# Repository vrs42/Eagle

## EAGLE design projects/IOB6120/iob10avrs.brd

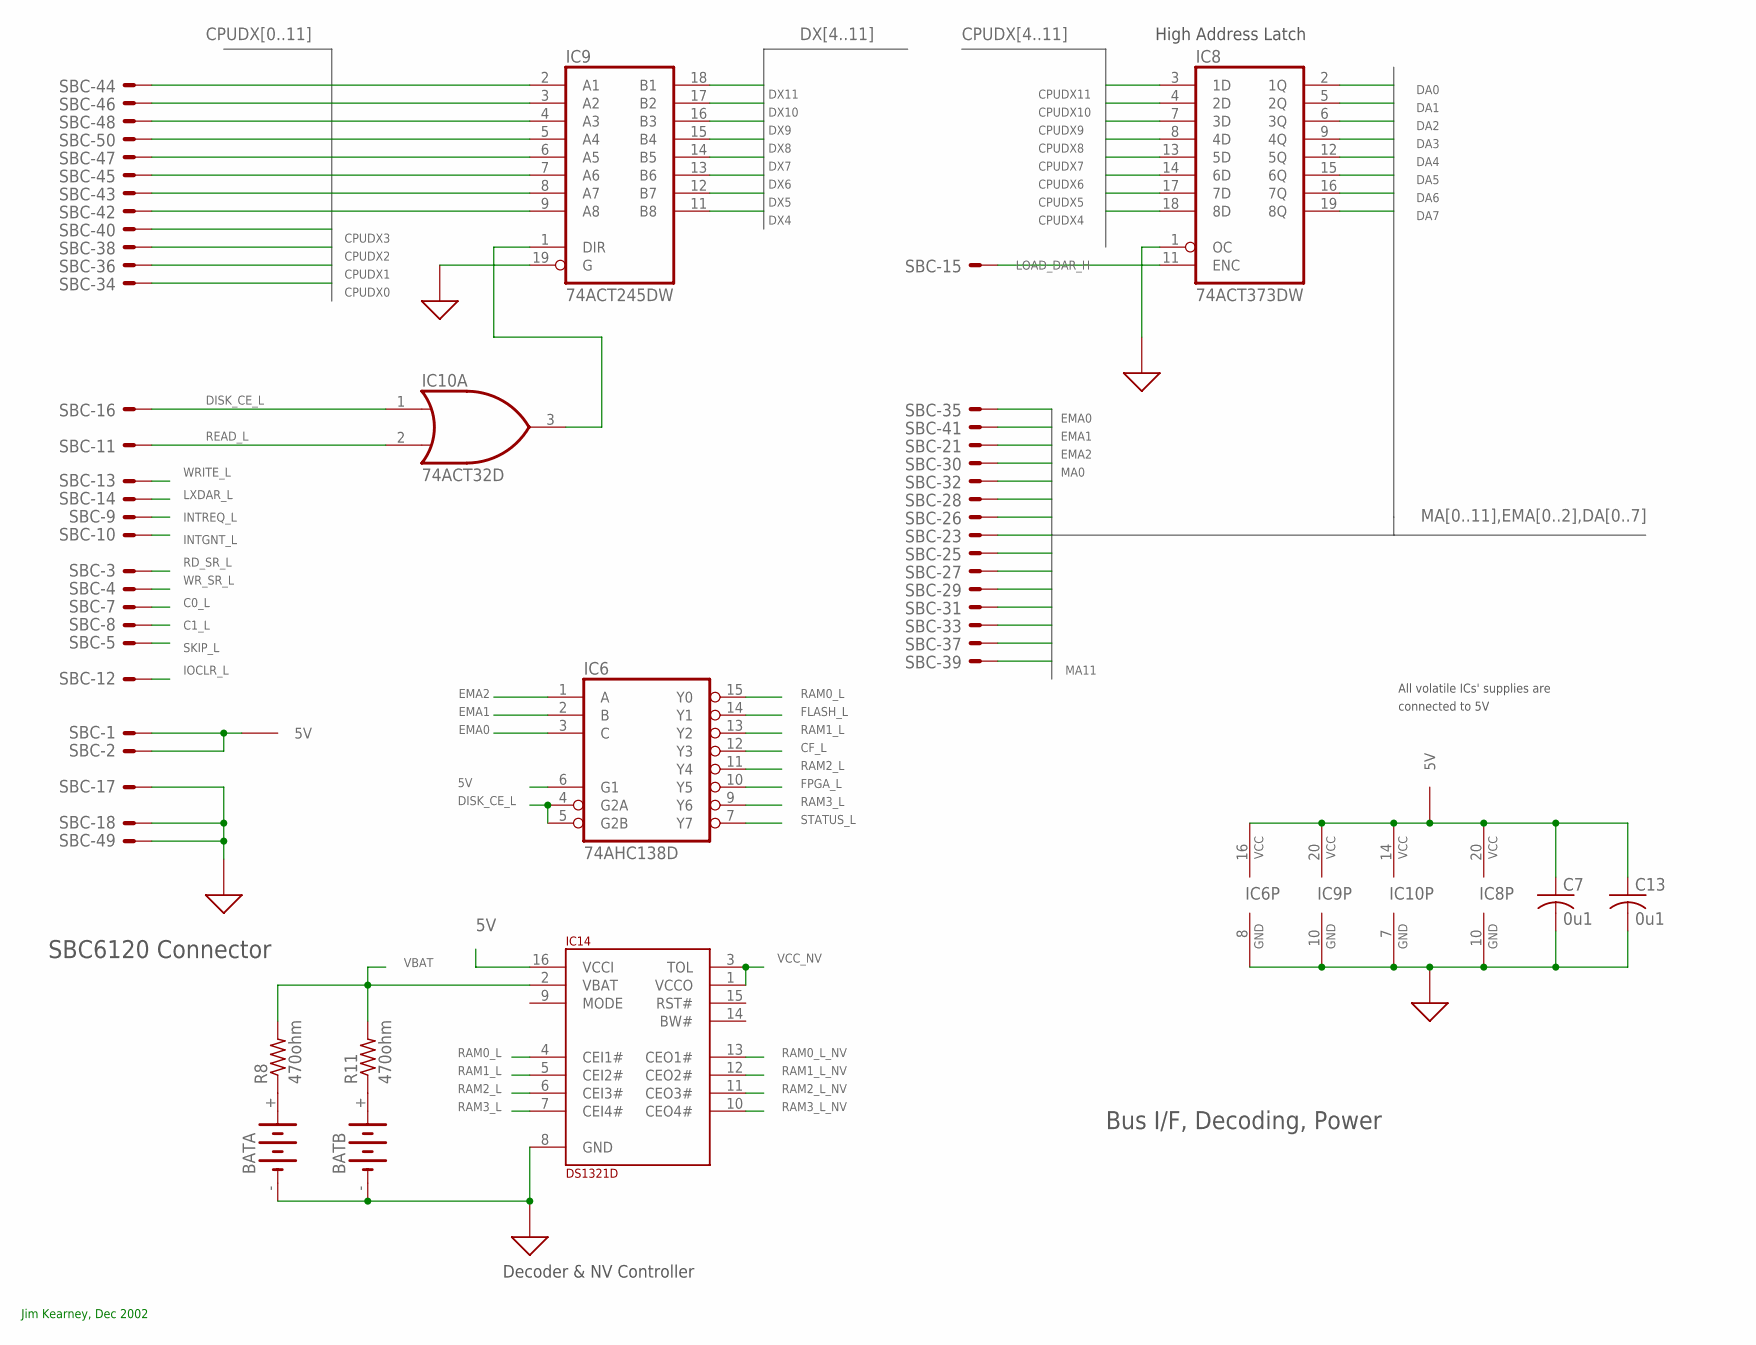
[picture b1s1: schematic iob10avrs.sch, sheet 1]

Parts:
BATA: CR2032HOLDER
BATB: CR2032HOLDER
C7, C13: 0u1; C0805
IC6: 74AHC138D; SO16
IC8: 74ACT373DW; SO20W
IC9: 74ACT245DW; SO20W
IC10: 74ACT32D; SO14
IC14: DS1321D; SO16
R8, R11: 470ohm; M0805
SBC: 50E; ML50

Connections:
5V: C7.1, C13.1, IC6.6 (G1), IC6.16 (VCC), IC8.20 (VCC), IC9.20 (VCC), IC10.14 (VCC), IC14.16 (VCCI), SBC.1, SBC.2; also elsewhere on the board
C0_L: SBC.7; also elsewhere on the board
C1_L: SBC.8; also elsewhere on the board
CF_L: IC6.12 (Y3); also elsewhere on the board
CPUDX0: SBC.34; also elsewhere on the board
CPUDX1: SBC.36; also elsewhere on the board
CPUDX2: SBC.38; also elsewhere on the board
CPUDX3: SBC.40; also elsewhere on the board
CPUDX4: IC8.18 (8D), IC9.9 (A8), SBC.42; also elsewhere on the board
CPUDX5: IC8.17 (7D), IC9.8 (A7), SBC.43; also elsewhere on the board
CPUDX6: IC8.14 (6D), IC9.7 (A6), SBC.45; also elsewhere on the board
CPUDX7: IC8.13 (5D), IC9.6 (A5), SBC.47; also elsewhere on the board
CPUDX8: IC8.8 (4D), IC9.5 (A4), SBC.50; also elsewhere on the board
CPUDX9: IC8.7 (3D), IC9.4 (A3), SBC.48; also elsewhere on the board
CPUDX10: IC8.4 (2D), IC9.3 (A2), SBC.46; also elsewhere on the board
CPUDX11: IC8.3 (1D), IC9.2 (A1), SBC.44; also elsewhere on the board
DA0: IC8.2 (1Q); also elsewhere on the board
DA1: IC8.5 (2Q); also elsewhere on the board
DA2: IC8.6 (3Q); also elsewhere on the board
DA3: IC8.9 (4Q); also elsewhere on the board
DA4: IC8.12 (5Q); also elsewhere on the board
DA5: IC8.15 (6Q); also elsewhere on the board
DA6: IC8.16 (7Q); also elsewhere on the board
DA7: IC8.19 (8Q)
DISK_CE_L: IC6.4 (G2A), IC6.5 (G2B), IC10.1 (I0), SBC.16
DX4: IC9.11 (B8); also elsewhere on the board
DX5: IC9.12 (B7); also elsewhere on the board
DX6: IC9.13 (B6); also elsewhere on the board
DX7: IC9.14 (B5); also elsewhere on the board
DX8: IC9.15 (B4); also elsewhere on the board
DX9: IC9.16 (B3); also elsewhere on the board
DX10: IC9.17 (B2); also elsewhere on the board
DX11: IC9.18 (B1); also elsewhere on the board
EMA0: IC6.3 (C), SBC.35
EMA1: IC6.2 (B), SBC.41
EMA2: IC6.1 (A), SBC.21
FLASH_L: IC6.14 (Y1); also elsewhere on the board
FPGA_L: IC6.10 (Y5); also elsewhere on the board
GND: BATA.-, BATB.-, C7.2, C13.2, IC6.8 (GND), IC8.1 (OC), IC8.10 (GND), IC9.10 (GND), IC9.19 (G), IC10.7 (GND), IC14.8 (GND), SBC.17, SBC.18, SBC.49; also elsewhere on the board
INTGNT_L: SBC.10; also elsewhere on the board
INTREQ_L: SBC.9; also elsewhere on the board
IOCLR_L: SBC.12; also elsewhere on the board
LOAD_DAR_H: IC8.11 (ENC), SBC.15
LXDAR_L: SBC.14; also elsewhere on the board
MA0: SBC.30; also elsewhere on the board
MA1: SBC.32; also elsewhere on the board
MA2: SBC.28; also elsewhere on the board
MA3: SBC.26; also elsewhere on the board
MA4: SBC.23; also elsewhere on the board
MA5: SBC.25; also elsewhere on the board
MA6: SBC.27; also elsewhere on the board
MA7: SBC.29; also elsewhere on the board
MA8: SBC.31; also elsewhere on the board
MA9: SBC.33; also elsewhere on the board
MA10: SBC.37; also elsewhere on the board
MA11: SBC.39; also elsewhere on the board
unnamed: BATA.+, R8.1
unnamed: BATB.+, R11.1
unnamed: IC9.1 (DIR), IC10.3 (O)
RAM0_L: IC6.15 (Y0), IC14.4 (CEI1#)
RAM0_L_NV: IC14.13 (CEO1#); also elsewhere on the board
RAM1_L: IC6.13 (Y2), IC14.5 (CEI2#)
RAM1_L_NV: IC14.12 (CEO2#); also elsewhere on the board
RAM2_L: IC6.11 (Y4), IC14.6 (CEI3#)
RAM2_L_NV: IC14.11 (CEO3#); also elsewhere on the board
RAM3_L: IC6.9 (Y6), IC14.7 (CEI4#)
RAM3_L_NV: IC14.10 (CEO4#); also elsewhere on the board
RD_SR_L: SBC.3; also elsewhere on the board
READ_L: IC10.2 (I1), SBC.11; also elsewhere on the board
SKIP_L: SBC.5; also elsewhere on the board
STATUS_L: IC6.7 (Y7); also elsewhere on the board
VBAT: IC14.2 (VBAT), R8.2, R11.2; also elsewhere on the board
VCC_NV: IC14.1 (VCCO), IC14.3 (TOL); also elsewhere on the board
WRITE_L: SBC.13; also elsewhere on the board
WR_SR_L: SBC.4; also elsewhere on the board

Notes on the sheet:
High Address Latch
Bus I/F, Decoding, Power
All volatile ICs' supplies are
connected to 5V
Jim Kearney, Dec 2002
SBC6120 Connector
Decoder & NV Controller

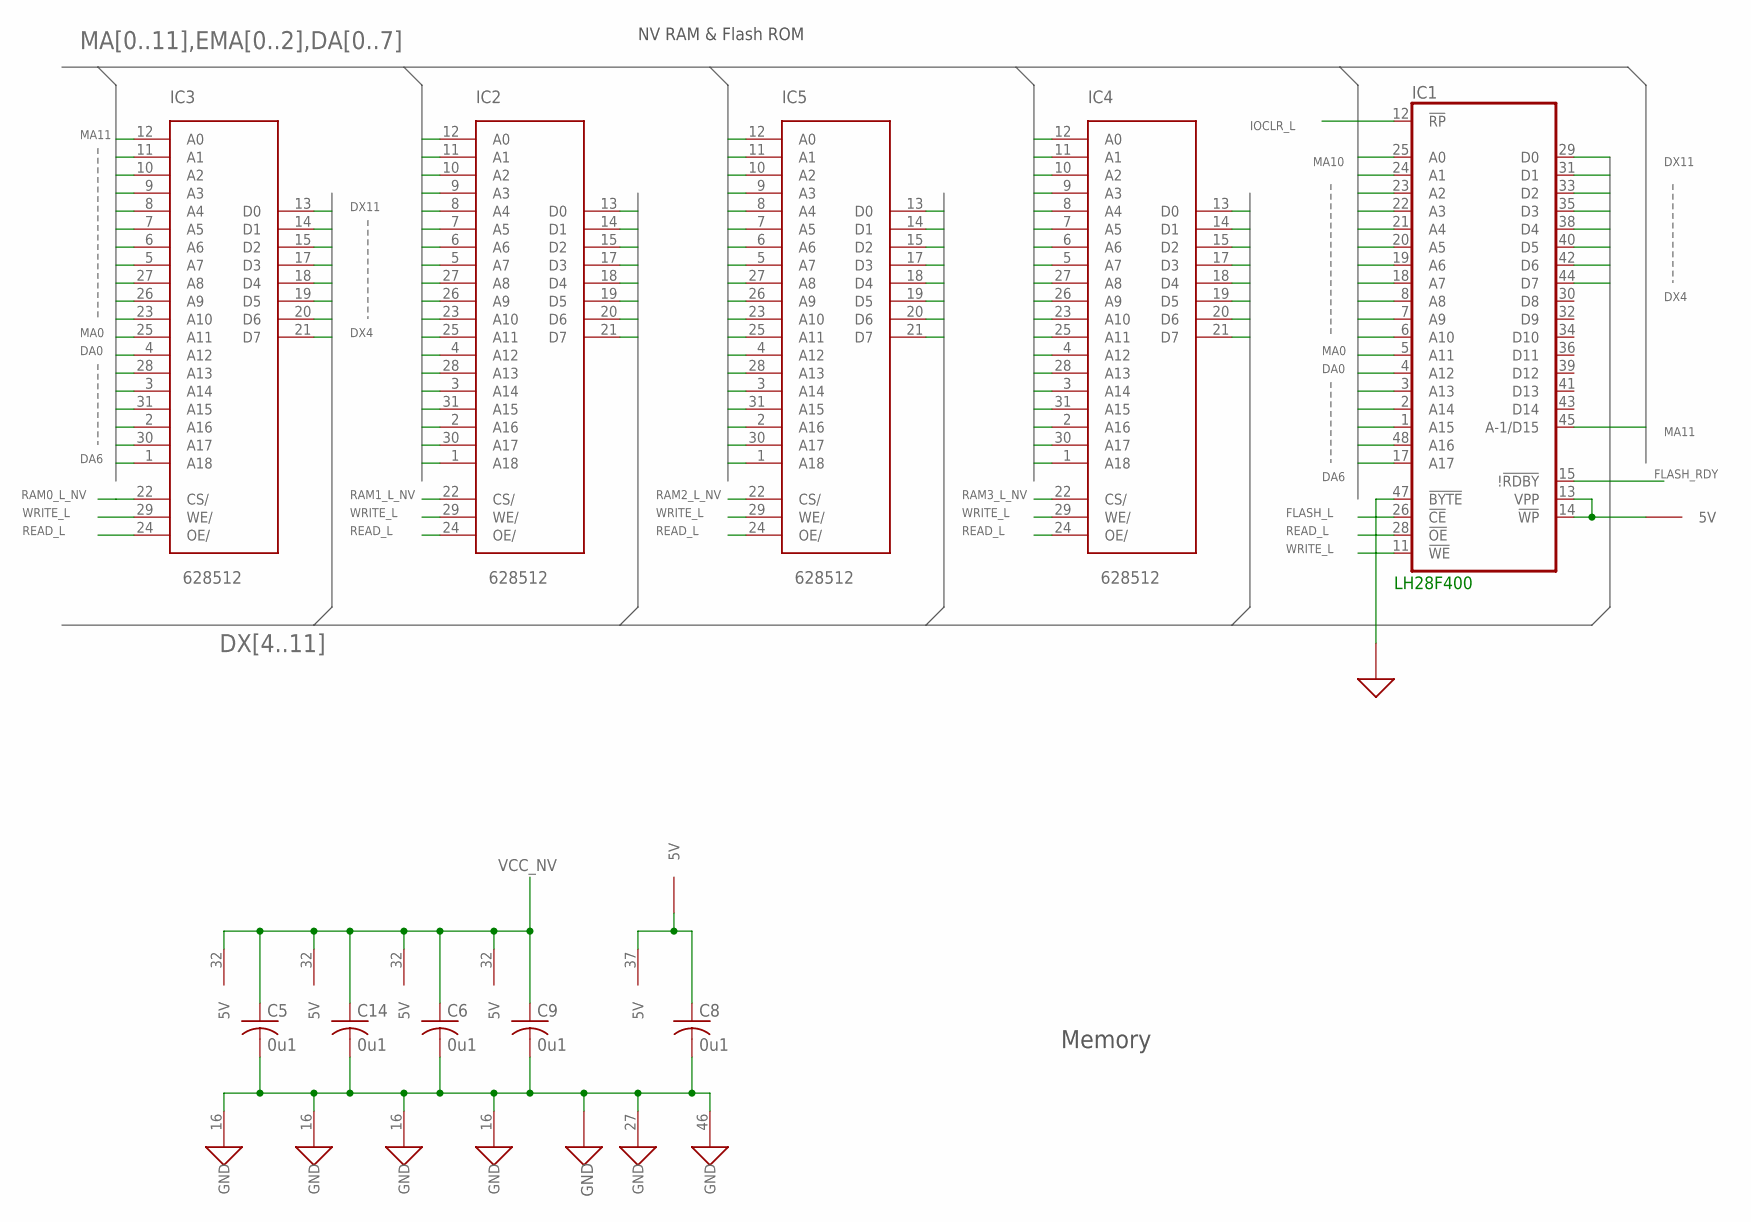
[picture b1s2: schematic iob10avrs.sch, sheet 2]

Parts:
C5, C6, C8, C9, C14: 0u1; C0805
IC1: LH28F400; TSOP48
IC2, IC3, IC4, IC5: 628512; SOP32

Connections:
5V: C8.1, IC1.13 (VPP), IC1.14 (!WP), IC1.37 (5V); also elsewhere on the board
DA0: IC1.5 (A11), IC2.4 (A12), IC3.4 (A12), IC4.4 (A12), IC5.4 (A12); also elsewhere on the board
DA1: IC1.4 (A12), IC2.28 (A13), IC3.28 (A13), IC4.28 (A13), IC5.28 (A13); also elsewhere on the board
DA2: IC1.3 (A13), IC2.3 (A14), IC3.3 (A14), IC4.3 (A14), IC5.3 (A14); also elsewhere on the board
DA3: IC1.2 (A14), IC2.31 (A15), IC3.31 (A15), IC4.31 (A15), IC5.31 (A15); also elsewhere on the board
DA4: IC1.1 (A15), IC2.2 (A16), IC3.2 (A16), IC4.2 (A16), IC5.2 (A16); also elsewhere on the board
DA5: IC1.48 (A16), IC2.30 (A17), IC3.30 (A17), IC4.30 (A17), IC5.30 (A17); also elsewhere on the board
DA6: IC1.17 (A17), IC2.1 (A18), IC3.1 (A18), IC4.1 (A18), IC5.1 (A18); also elsewhere on the board
DX4: IC1.44 (D7), IC2.21 (D7), IC3.21 (D7), IC4.21 (D7), IC5.21 (D7); also elsewhere on the board
DX5: IC1.42 (D6), IC2.20 (D6), IC3.20 (D6), IC4.20 (D6), IC5.20 (D6); also elsewhere on the board
DX6: IC1.40 (D5), IC2.19 (D5), IC3.19 (D5), IC4.19 (D5), IC5.19 (D5); also elsewhere on the board
DX7: IC1.38 (D4), IC2.18 (D4), IC3.18 (D4), IC4.18 (D4), IC5.18 (D4); also elsewhere on the board
DX8: IC1.35 (D3), IC2.17 (D3), IC3.17 (D3), IC4.17 (D3), IC5.17 (D3); also elsewhere on the board
DX9: IC1.33 (D2), IC2.15 (D2), IC3.15 (D2), IC4.15 (D2), IC5.15 (D2); also elsewhere on the board
DX10: IC1.31 (D1), IC2.14 (D1), IC3.14 (D1), IC4.14 (D1), IC5.14 (D1); also elsewhere on the board
DX11: IC1.29 (D0), IC2.13 (D0), IC3.13 (D0), IC4.13 (D0), IC5.13 (D0); also elsewhere on the board
FLASH_L: IC1.26 (!CE); also elsewhere on the board
FLASH_RDY: IC1.15 (!!RDBY); also elsewhere on the board
GND: C5.2, C6.2, C8.2, C9.2, C14.2, IC1.27 (GND), IC1.46 (GND), IC1.47 (!BYTE), IC2.16 (GND), IC3.16 (GND), IC4.16 (GND), IC5.16 (GND); also elsewhere on the board
IOCLR_L: IC1.12 (!RP); also elsewhere on the board
MA0: IC1.6 (A10), IC2.25 (A11), IC3.25 (A11), IC4.25 (A11), IC5.25 (A11); also elsewhere on the board
MA1: IC1.7 (A9), IC2.23 (A10), IC3.23 (A10), IC4.23 (A10), IC5.23 (A10); also elsewhere on the board
MA2: IC1.8 (A8), IC2.26 (A9), IC3.26 (A9), IC4.26 (A9), IC5.26 (A9); also elsewhere on the board
MA3: IC1.18 (A7), IC2.27 (A8), IC3.27 (A8), IC4.27 (A8), IC5.27 (A8); also elsewhere on the board
MA4: IC1.19 (A6), IC2.5 (A7), IC3.5 (A7), IC4.5 (A7), IC5.5 (A7); also elsewhere on the board
MA5: IC1.20 (A5), IC2.6 (A6), IC3.6 (A6), IC4.6 (A6), IC5.6 (A6); also elsewhere on the board
MA6: IC1.21 (A4), IC2.7 (A5), IC3.7 (A5), IC4.7 (A5), IC5.7 (A5); also elsewhere on the board
MA7: IC1.22 (A3), IC2.8 (A4), IC3.8 (A4), IC4.8 (A4), IC5.8 (A4); also elsewhere on the board
MA8: IC1.23 (A2), IC2.9 (A3), IC3.9 (A3), IC4.9 (A3), IC5.9 (A3); also elsewhere on the board
MA9: IC1.24 (A1), IC2.10 (A2), IC3.10 (A2), IC4.10 (A2), IC5.10 (A2); also elsewhere on the board
MA10: IC1.25 (A0), IC2.11 (A1), IC3.11 (A1), IC4.11 (A1), IC5.11 (A1); also elsewhere on the board
MA11: IC1.45 (A-1/D15), IC2.12 (A0), IC3.12 (A0), IC4.12 (A0), IC5.12 (A0); also elsewhere on the board
RAM0_L_NV: IC3.22 (CS/); also elsewhere on the board
RAM1_L_NV: IC2.22 (CS/); also elsewhere on the board
RAM2_L_NV: IC5.22 (CS/); also elsewhere on the board
RAM3_L_NV: IC4.22 (CS/); also elsewhere on the board
READ_L: IC1.28 (!OE), IC2.24 (OE/), IC3.24 (OE/), IC4.24 (OE/), IC5.24 (OE/); also elsewhere on the board
VCC_NV: C5.1, C6.1, C9.1, C14.1, IC2.32 (5V), IC3.32 (5V), IC4.32 (5V), IC5.32 (5V); also elsewhere on the board
WRITE_L: IC1.11 (!WE), IC2.29 (WE/), IC3.29 (WE/), IC4.29 (WE/), IC5.29 (WE/); also elsewhere on the board

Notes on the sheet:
Memory
NV RAM & Flash ROM
LH28F400

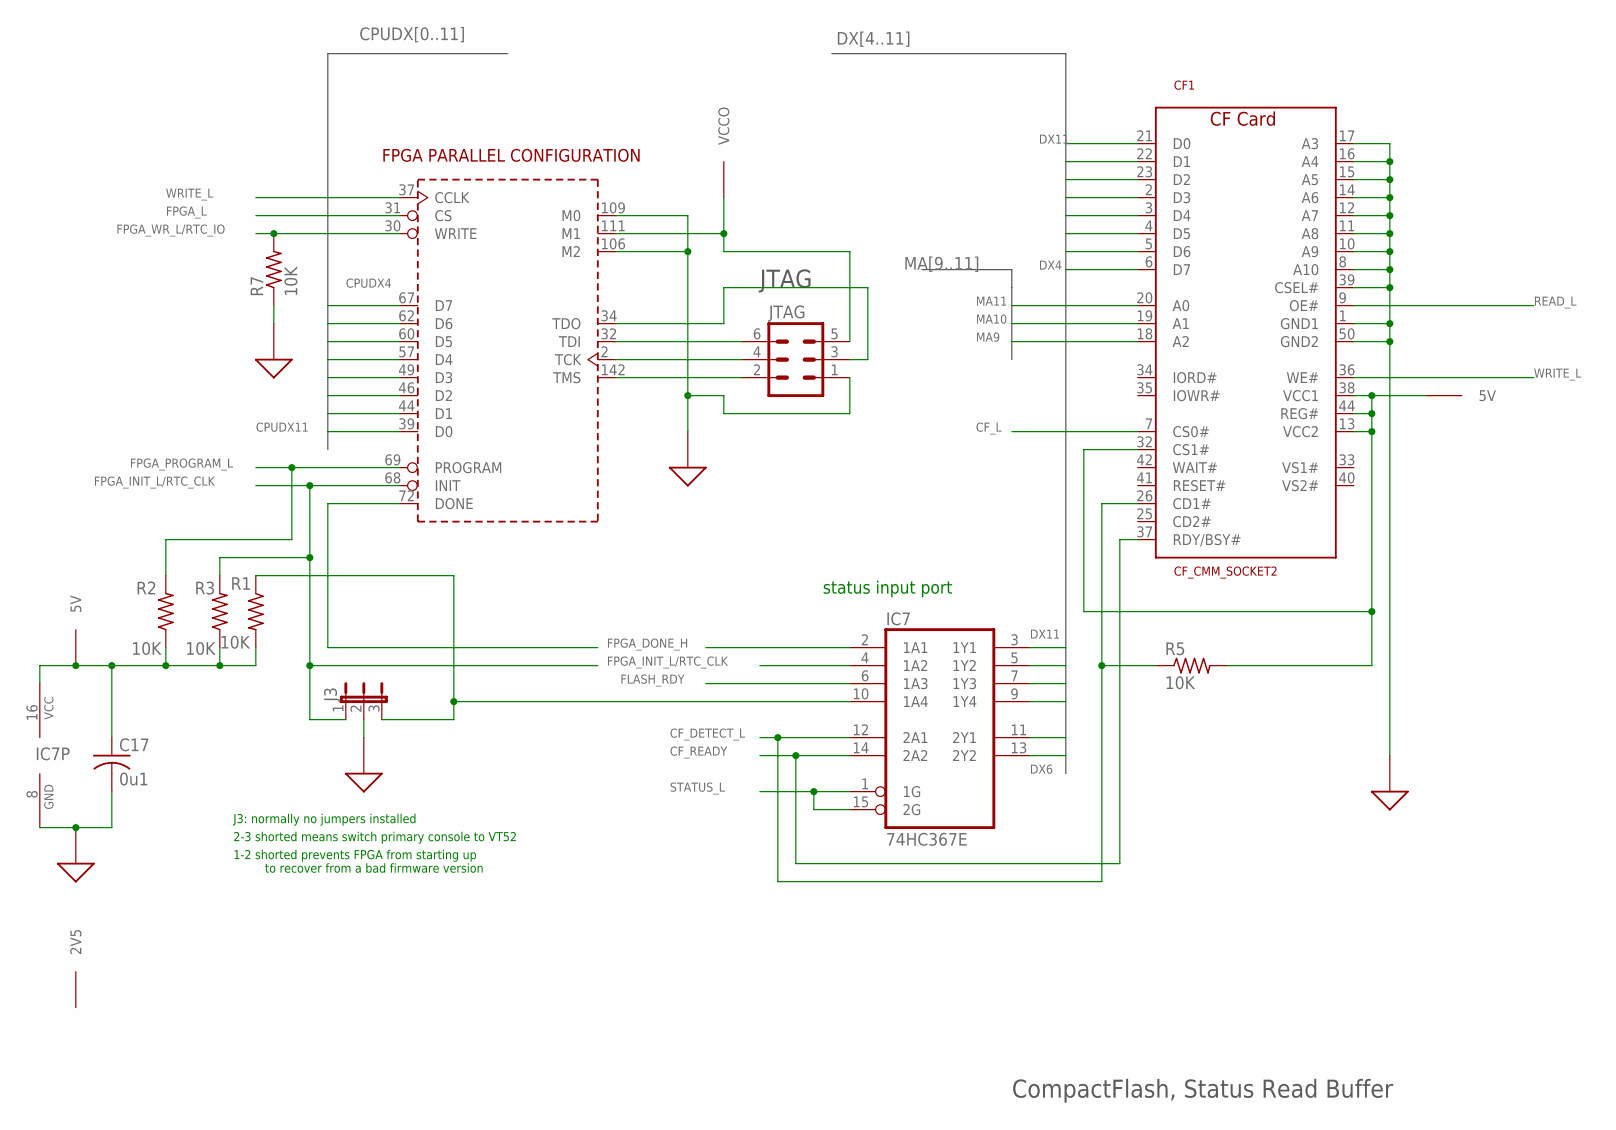
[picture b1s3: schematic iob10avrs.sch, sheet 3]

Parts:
C17: 0u1; C0805
CF1: CF_CMM_SOCKET2; CF_SOCKET2_SMT
IC7: 74HC367E; SO16
IC12: XC2S100-5TQ144C; TQFP144
J3: JP2E; JP2
JTAG: MA03-2
R1, R2, R3, R7: 10K; M0805
R5: 10K; R0805

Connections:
2V5: IC12.9 (2V5), IC12.14 (2V5), IC12.24 (2V5), IC12.55 (2V5), IC12.82 (2V5), IC12.92 (2V5), IC12.97 (2V5), IC12.125 (2V5); also elsewhere on the board
5V: C17.1, CF1.13 (VCC2), CF1.32 (CS1#), CF1.38 (VCC1), CF1.44 (REG#), IC7.16 (VCC), R1.2, R2.1, R3.1, R5.2; also elsewhere on the board
CF_DETECT_L: CF1.26 (CD1#), IC7.12 (2A1), R5.1
CF_L: CF1.7 (CS0#); also elsewhere on the board
CF_READY: CF1.37 (RDY/BSY#), IC7.14 (2A2)
CPUDX4: IC12.67 (D7); also elsewhere on the board
CPUDX5: IC12.62 (D6); also elsewhere on the board
CPUDX6: IC12.60 (D5); also elsewhere on the board
CPUDX7: IC12.57 (D4); also elsewhere on the board
CPUDX8: IC12.49 (D3); also elsewhere on the board
CPUDX9: IC12.46 (D2); also elsewhere on the board
CPUDX10: IC12.44 (D1); also elsewhere on the board
CPUDX11: IC12.39 (D0); also elsewhere on the board
DX4: CF1.6 (D7); also elsewhere on the board
DX5: CF1.5 (D6); also elsewhere on the board
DX6: CF1.4 (D5), IC7.13 (2Y2); also elsewhere on the board
DX7: CF1.3 (D4), IC7.11 (2Y1); also elsewhere on the board
DX8: CF1.2 (D3), IC7.9 (1Y4); also elsewhere on the board
DX9: CF1.23 (D2), IC7.7 (1Y3); also elsewhere on the board
DX10: CF1.22 (D1), IC7.5 (1Y2); also elsewhere on the board
DX11: CF1.21 (D0), IC7.3 (1Y1); also elsewhere on the board
FLASH_RDY: IC7.6 (1A3); also elsewhere on the board
FPGA_DONE_H: IC7.2 (1A1), IC12.72 (DONE)
FPGA_INIT_L/RTC_CLK: IC7.4 (1A2), IC12.68 (INIT), J3.1, R3.2; also elsewhere on the board
FPGA_L: IC12.31 (CS); also elsewhere on the board
FPGA_PROGRAM_L: IC12.69 (PROGRAM), R2.2; also elsewhere on the board
FPGA_WR_L/RTC_IO: IC12.30 (WRITE), R7.2; also elsewhere on the board
GND: C17.2, CF1.1 (GND1), CF1.8 (A10), CF1.10 (A9), CF1.11 (A8), CF1.12 (A7), CF1.14 (A6), CF1.15 (A5), CF1.16 (A4), CF1.17 (A3), CF1.39 (CSEL#), CF1.50 (GND2), IC7.8 (GND), IC12.8 (GND), IC12.17 (GND), IC12.25 (GND), IC12.33 (GND), IC12.45 (GND), IC12.52 (GND), IC12.61 (GND), IC12.73 (GND), IC12.81 (GND), IC12.89 (GND), IC12.98 (GND), IC12.106 (M2), IC12.109 (M0), IC12.110 (GND), IC12.119 (GND), IC12.128 (GND), IC12.135 (GND), IC12.143 (GND), J3.2, JTAG.1, R7.1; also elsewhere on the board
MA9: CF1.18 (A2); also elsewhere on the board
MA10: CF1.19 (A1); also elsewhere on the board
MA11: CF1.20 (A0); also elsewhere on the board
unnamed: IC7.10 (1A4), J3.3, R1.1
READ_L: CF1.9 (OE#); also elsewhere on the board
STATUS_L: IC7.1 (1G), IC7.15 (2G); also elsewhere on the board
TCK: IC12.2 (TCK), JTAG.4
TDI: IC12.32 (TDI), JTAG.6
TDO: IC12.34 (TDO), JTAG.3
TMS: IC12.142 (TMS), JTAG.2
VCCO: IC12.1 (VCCO), IC12.16 (VCCO), IC12.35 (VCCO), IC12.36 (VCCO), IC12.53 (VCCO), IC12.70 (VCCO), IC12.71 (VCCO), IC12.90 (VCCO), IC12.107 (VCCO), IC12.108 (VCCO), IC12.111 (M1), IC12.127 (VCCO), IC12.144 (VCCO), JTAG.5; also elsewhere on the board
WRITE_L: CF1.36 (WE#), IC12.37 (CCLK); also elsewhere on the board

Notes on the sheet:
CompactFlash, Status Read Buffer
JTAG
status input port
J3: normally no jumpers installed
2-3 shorted means switch primary console to VT52
1-2 shorted prevents FPGA from starting up
to recover from a bad firmware version

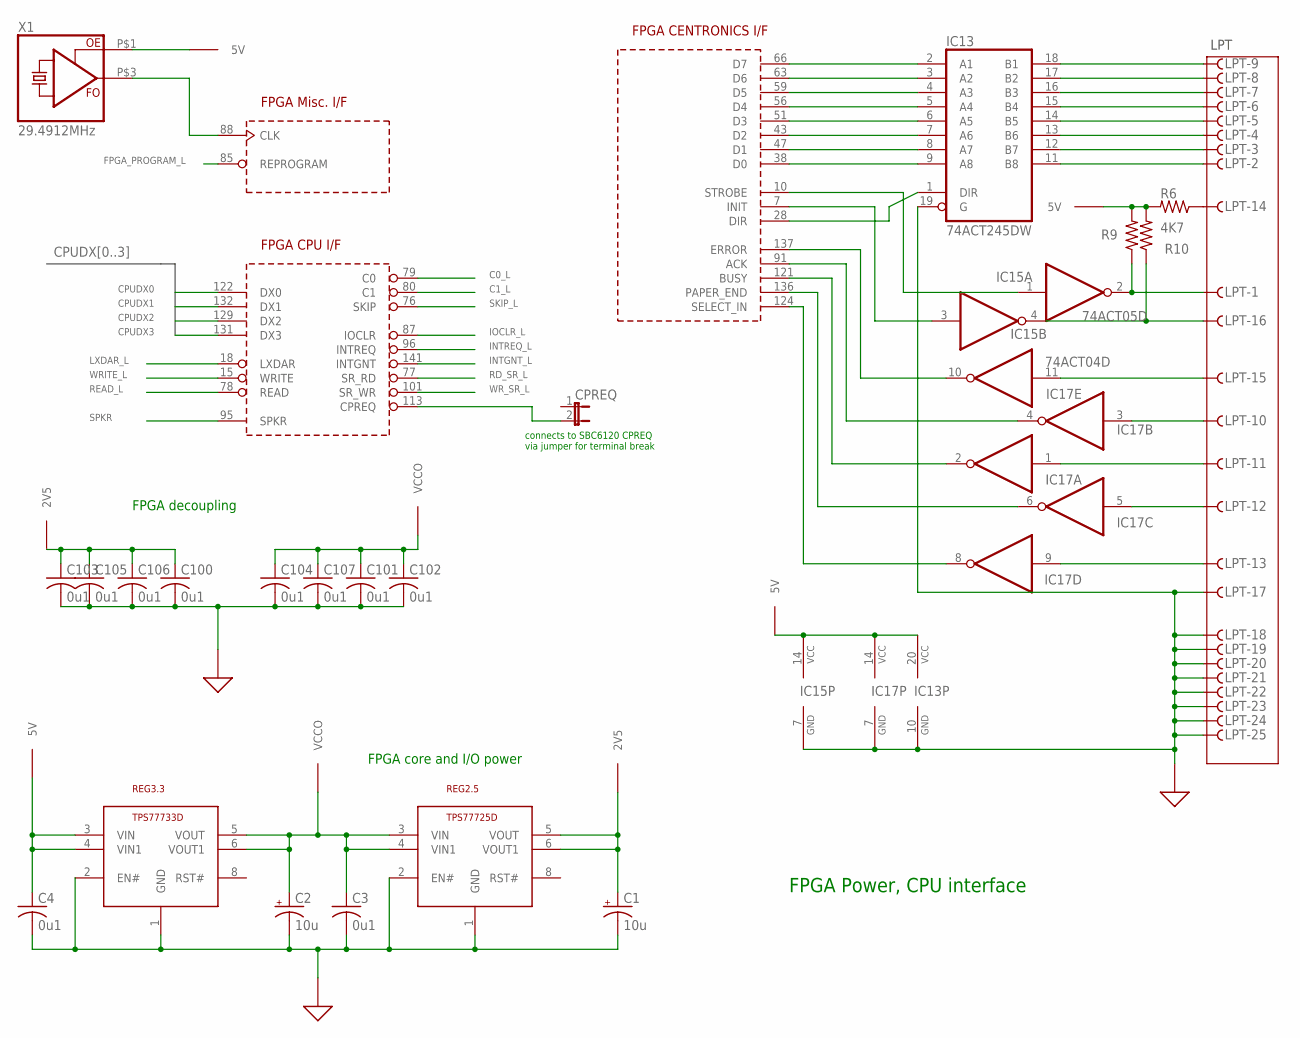
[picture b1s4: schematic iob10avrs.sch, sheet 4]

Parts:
C1, C2: 10u; D/7343-31W
C3, C4, C100, C101, C102, C103, C104, C105, C106, C107: 0u1; C0805
CPREQ: JP1E; JP1
IC12: XC2S100-5TQ144C; TQFP144
IC13: 74ACT245DW; SO20W
IC15: 74ACT05D; SO14
IC17: 74ACT04D; SO14
LPT: F25HS; F25H
R6, R9, R10: 4K7; M0805
REG2.5: TPS77725D; SO08
REG3.3: TPS77733D; SO08
X1: 29.4912MHz; SG636

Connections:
2V5: C1.+, C100.1, C103.1, C105.1, C106.1, IC12.9 (2V5), IC12.14 (2V5), IC12.24 (2V5), IC12.55 (2V5), IC12.82 (2V5), IC12.92 (2V5), IC12.97 (2V5), IC12.125 (2V5), REG2.5.5 (VOUT), REG2.5.6 (VOUT1)
5V: C4.1, IC13.20 (VCC), IC15.14 (VCC), IC17.14 (VCC), R6.2, R9.2, R10.2, REG3.3.3 (VIN), REG3.3.4 (VIN1), X1.P$1 (OE), X1.P$4 (5V); also elsewhere on the board
C0_L: IC12.79 (C0); also elsewhere on the board
C1_L: IC12.80 (C1); also elsewhere on the board
CPUDX0: IC12.122 (DX0); also elsewhere on the board
CPUDX1: IC12.132 (DX1); also elsewhere on the board
CPUDX2: IC12.129 (DX2); also elsewhere on the board
CPUDX3: IC12.131 (DX3); also elsewhere on the board
FPGA_PROGRAM_L: IC12.85 (REPROGRAM); also elsewhere on the board
GND: C1.-, C2.-, C3.2, C4.2, C100.2, C101.2, C102.2, C103.2, C104.2, C105.2, C106.2, C107.2, IC12.8 (GND), IC12.17 (GND), IC12.25 (GND), IC12.33 (GND), IC12.45 (GND), IC12.52 (GND), IC12.61 (GND), IC12.73 (GND), IC12.81 (GND), IC12.89 (GND), IC12.98 (GND), IC12.110 (GND), IC12.119 (GND), IC12.128 (GND), IC12.135 (GND), IC12.143 (GND), IC13.10 (GND), IC13.19 (G), IC15.7 (GND), IC17.7 (GND), LPT.17, LPT.18, LPT.19, LPT.20, LPT.21, LPT.22, LPT.23, LPT.24, LPT.25, REG2.5.1 (GND), REG2.5.2 (EN#), REG3.3.1 (GND), REG3.3.2 (EN#), X1.P$2 (GND); also elsewhere on the board
INTGNT_L: IC12.141 (INTGNT); also elsewhere on the board
INTREQ_L: IC12.96 (INTREQ); also elsewhere on the board
IOCLR_L: IC12.87 (IOCLR); also elsewhere on the board
LXDAR_L: IC12.18 (LXDAR); also elsewhere on the board
unnamed: IC12.66 (D7), IC13.2 (A1)
unnamed: IC12.63 (D6), IC13.3 (A2)
unnamed: IC12.59 (D5), IC13.4 (A3)
unnamed: IC12.56 (D4), IC13.5 (A4)
unnamed: IC12.88 (CLK), X1.P$3 (FO)
unnamed: IC12.51 (D3), IC13.6 (A5)
unnamed: IC12.43 (D2), IC13.7 (A6)
unnamed: IC12.47 (D1), IC13.8 (A7)
unnamed: IC12.38 (D0), IC13.9 (A8)
unnamed: IC12.28 (DIR), IC13.1 (DIR)
unnamed: IC12.7 (INIT), IC15.3 (I)
unnamed: IC12.10 (STROBE), IC15.1 (I)
unnamed: IC12.137 (ERROR), IC17.10 (O)
unnamed: IC12.91 (ACK), IC17.4 (O)
unnamed: IC12.121 (BUSY), IC17.2 (O)
unnamed: IC12.136 (PAPER_END), IC17.6 (O)
unnamed: IC12.124 (SELECT_IN), IC17.8 (O)
unnamed: IC13.18 (B1), LPT.9
unnamed: IC13.17 (B2), LPT.8
unnamed: IC13.16 (B3), LPT.7
unnamed: IC13.15 (B4), LPT.6
unnamed: IC13.14 (B5), LPT.5
unnamed: IC13.13 (B6), LPT.4
unnamed: IC13.12 (B7), LPT.3
unnamed: IC13.11 (B8), LPT.2
unnamed: IC15.2 (O), LPT.1, R9.1
unnamed: IC15.4 (O), LPT.16, R10.1
unnamed: IC17.11 (I), LPT.15
unnamed: IC17.3 (I), LPT.10
unnamed: IC17.1 (I), LPT.11
unnamed: IC17.5 (I), LPT.12
unnamed: IC17.9 (I), LPT.13
unnamed: LPT.14, R6.1
unnamed: CPREQ.2, IC12.113 (CPREQ)
RD_SR_L: IC12.77 (SR_RD); also elsewhere on the board
READ_L: IC12.78 (READ); also elsewhere on the board
SKIP_L: IC12.76 (SKIP); also elsewhere on the board
SPKR: IC12.95 (SPKR); also elsewhere on the board
VCCO: C2.+, C3.1, C101.1, C102.1, C104.1, C107.1, IC12.1 (VCCO), IC12.16 (VCCO), IC12.35 (VCCO), IC12.36 (VCCO), IC12.53 (VCCO), IC12.70 (VCCO), IC12.71 (VCCO), IC12.90 (VCCO), IC12.107 (VCCO), IC12.108 (VCCO), IC12.127 (VCCO), IC12.144 (VCCO), REG2.5.3 (VIN), REG2.5.4 (VIN1), REG3.3.5 (VOUT), REG3.3.6 (VOUT1); also elsewhere on the board
WRITE_L: IC12.15 (WRITE); also elsewhere on the board
WR_SR_L: IC12.101 (SR_WR); also elsewhere on the board

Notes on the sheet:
FPGA Power, CPU interface
FPGA decoupling
FPGA core and I/O power
LPT
connects to SBC6120 CPREQ
via jumper for terminal break

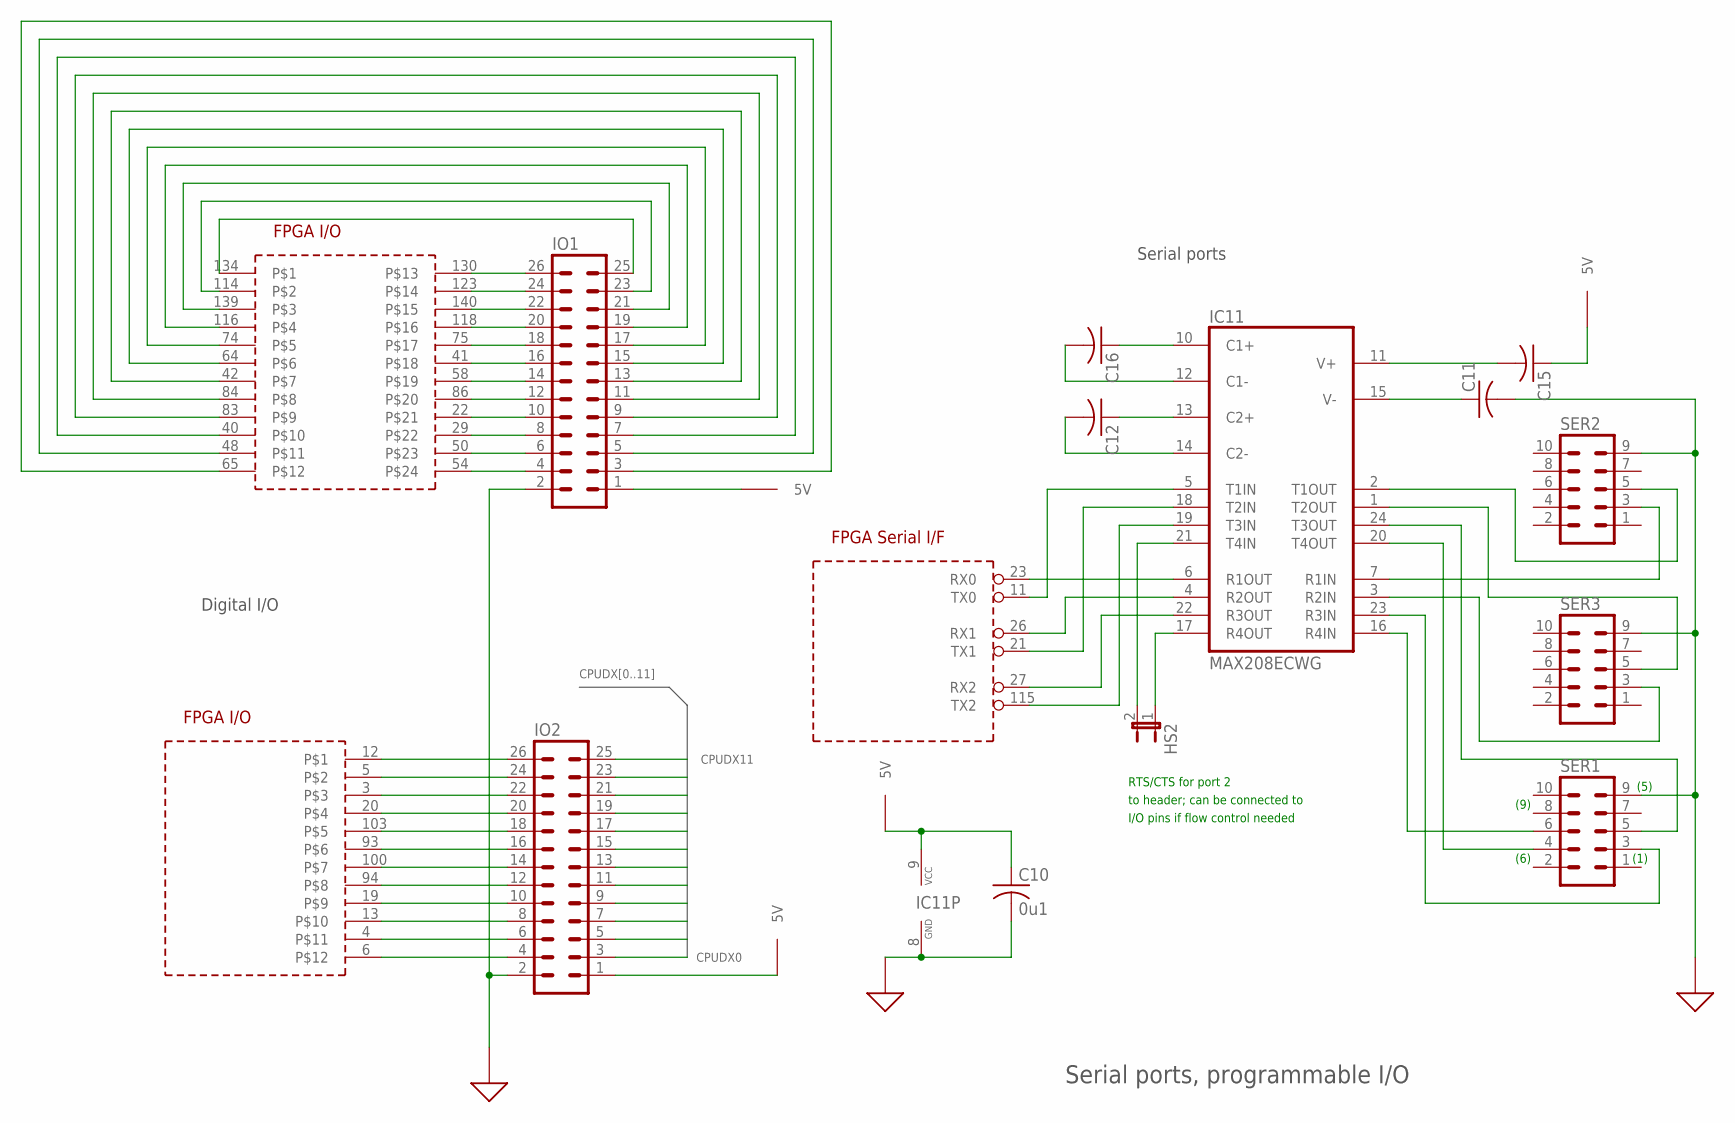
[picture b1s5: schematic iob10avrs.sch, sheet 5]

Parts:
C10: 0u1; C0805
C11, C12, C15, C16: C-USC1206; C1206
HS2: JP1E; JP1
IC11: MAX208ECWG; SO24L
IC12: XC2S100-5TQ144C; TQFP144
IO1, IO2: MA13-2
SER1, SER2, SER3: ML10

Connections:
2V5: IC12.9 (2V5), IC12.14 (2V5), IC12.24 (2V5), IC12.55 (2V5), IC12.82 (2V5), IC12.92 (2V5), IC12.97 (2V5), IC12.125 (2V5); also elsewhere on the board
5V: C10.1, C15.1, IC11.9 (VCC), IO1.1, IO2.1; also elsewhere on the board
CPUDX0: IO2.3; also elsewhere on the board
CPUDX1: IO2.5; also elsewhere on the board
CPUDX2: IO2.7; also elsewhere on the board
CPUDX3: IO2.9; also elsewhere on the board
CPUDX4: IO2.11; also elsewhere on the board
CPUDX5: IO2.13; also elsewhere on the board
CPUDX6: IO2.15; also elsewhere on the board
CPUDX7: IO2.17; also elsewhere on the board
CPUDX8: IO2.19; also elsewhere on the board
CPUDX9: IO2.21; also elsewhere on the board
CPUDX10: IO2.23; also elsewhere on the board
CPUDX11: IO2.25; also elsewhere on the board
CTS2: HS2.1, IC11.17 (R4OUT)
GND: C10.2, C11.2, IC11.8 (GND), IC12.8 (GND), IC12.17 (GND), IC12.25 (GND), IC12.33 (GND), IC12.45 (GND), IC12.52 (GND), IC12.61 (GND), IC12.73 (GND), IC12.81 (GND), IC12.89 (GND), IC12.98 (GND), IC12.110 (GND), IC12.119 (GND), IC12.128 (GND), IC12.135 (GND), IC12.143 (GND), IO1.2, IO2.2, SER1.9, SER2.9, SER3.9; also elsewhere on the board
unnamed: IC12.130, IO1.26
unnamed: IC12.123, IO1.24
unnamed: IC12.140, IO1.22
unnamed: IC12.118, IO1.20
unnamed: IC12.75, IO1.18
unnamed: IC12.41, IO1.16
unnamed: IC12.58, IO1.14
unnamed: IC12.86, IO1.12
unnamed: IC12.22, IO1.10
unnamed: IC12.29, IO1.8
unnamed: IC12.50, IO1.6
unnamed: IC12.54, IO1.4
unnamed: IC12.134, IO1.25
unnamed: IC12.114, IO1.23
unnamed: IC12.139, IO1.21
unnamed: IC12.116, IO1.19
unnamed: IC12.74, IO1.17
unnamed: IC12.64, IO1.15
unnamed: IC12.42, IO1.13
unnamed: IC12.84, IO1.11
unnamed: IC12.83, IO1.9
unnamed: IC12.40, IO1.7
unnamed: IC12.48, IO1.5
unnamed: IC12.65, IO1.3
unnamed: IC12.12, IO2.26
unnamed: IC12.5, IO2.24
unnamed: IC12.3, IO2.22
unnamed: IC12.20, IO2.20
unnamed: IC12.103, IO2.18
unnamed: IC12.93, IO2.16
unnamed: IC12.100, IO2.14
unnamed: IC11.16 (R4IN), SER1.6
unnamed: IC12.94, IO2.12
unnamed: IC12.19, IO2.10
unnamed: IC12.13, IO2.8
unnamed: IC12.4, IO2.6
unnamed: IC12.6, IO2.4
unnamed: IC11.6 (R1OUT), IC12.23 (RX0)
unnamed: IC11.5 (T1IN), IC12.11 (TX0)
unnamed: IC11.4 (R2OUT), IC12.26 (RX1)
unnamed: IC11.18 (T2IN), IC12.21 (TX1)
unnamed: IC11.22 (R3OUT), IC12.27 (RX2)
unnamed: IC11.19 (T3IN), IC12.115 (TX2)
unnamed: C16.1, IC11.10 (C1+)
unnamed: C16.2, IC11.12 (C1-)
unnamed: C12.1, IC11.13 (C2+)
unnamed: C12.2, IC11.14 (C2-)
unnamed: C15.2, IC11.11 (V+)
unnamed: C11.1, IC11.15 (V-)
unnamed: IC11.7 (R1IN), SER2.3
unnamed: IC11.3 (R2IN), SER3.3
unnamed: IC11.24 (T3OUT), SER1.5
unnamed: IC11.23 (R3IN), SER1.3
RTS2: HS2.2, IC11.21 (T4IN)
TX0: IC11.2 (T1OUT), SER2.5
TX1: IC11.1 (T2OUT), SER3.5
TX2: IC11.20 (T4OUT), SER1.4
VCCO: IC12.1 (VCCO), IC12.16 (VCCO), IC12.35 (VCCO), IC12.36 (VCCO), IC12.53 (VCCO), IC12.70 (VCCO), IC12.71 (VCCO), IC12.90 (VCCO), IC12.107 (VCCO), IC12.108 (VCCO), IC12.127 (VCCO), IC12.144 (VCCO); also elsewhere on the board

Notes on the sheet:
Serial ports, programmable I/O
Serial ports
Digital I/O
(1)
(5)
(6)
(9)
RTS/CTS for port 2
to header; can be connected to
I/O pins if flow control needed
